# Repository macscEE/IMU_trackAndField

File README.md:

TODO List:
PCB:
- [ ] Cambiare footprint switch da SMD a THT
- [ ] Controllare cosa ho a casa e cosa devo comprare

Programmazione:
- [ ] Capire come far vedere meglio i dati (velocità massima, altezza massima, altro?) -> Sito web al volo?

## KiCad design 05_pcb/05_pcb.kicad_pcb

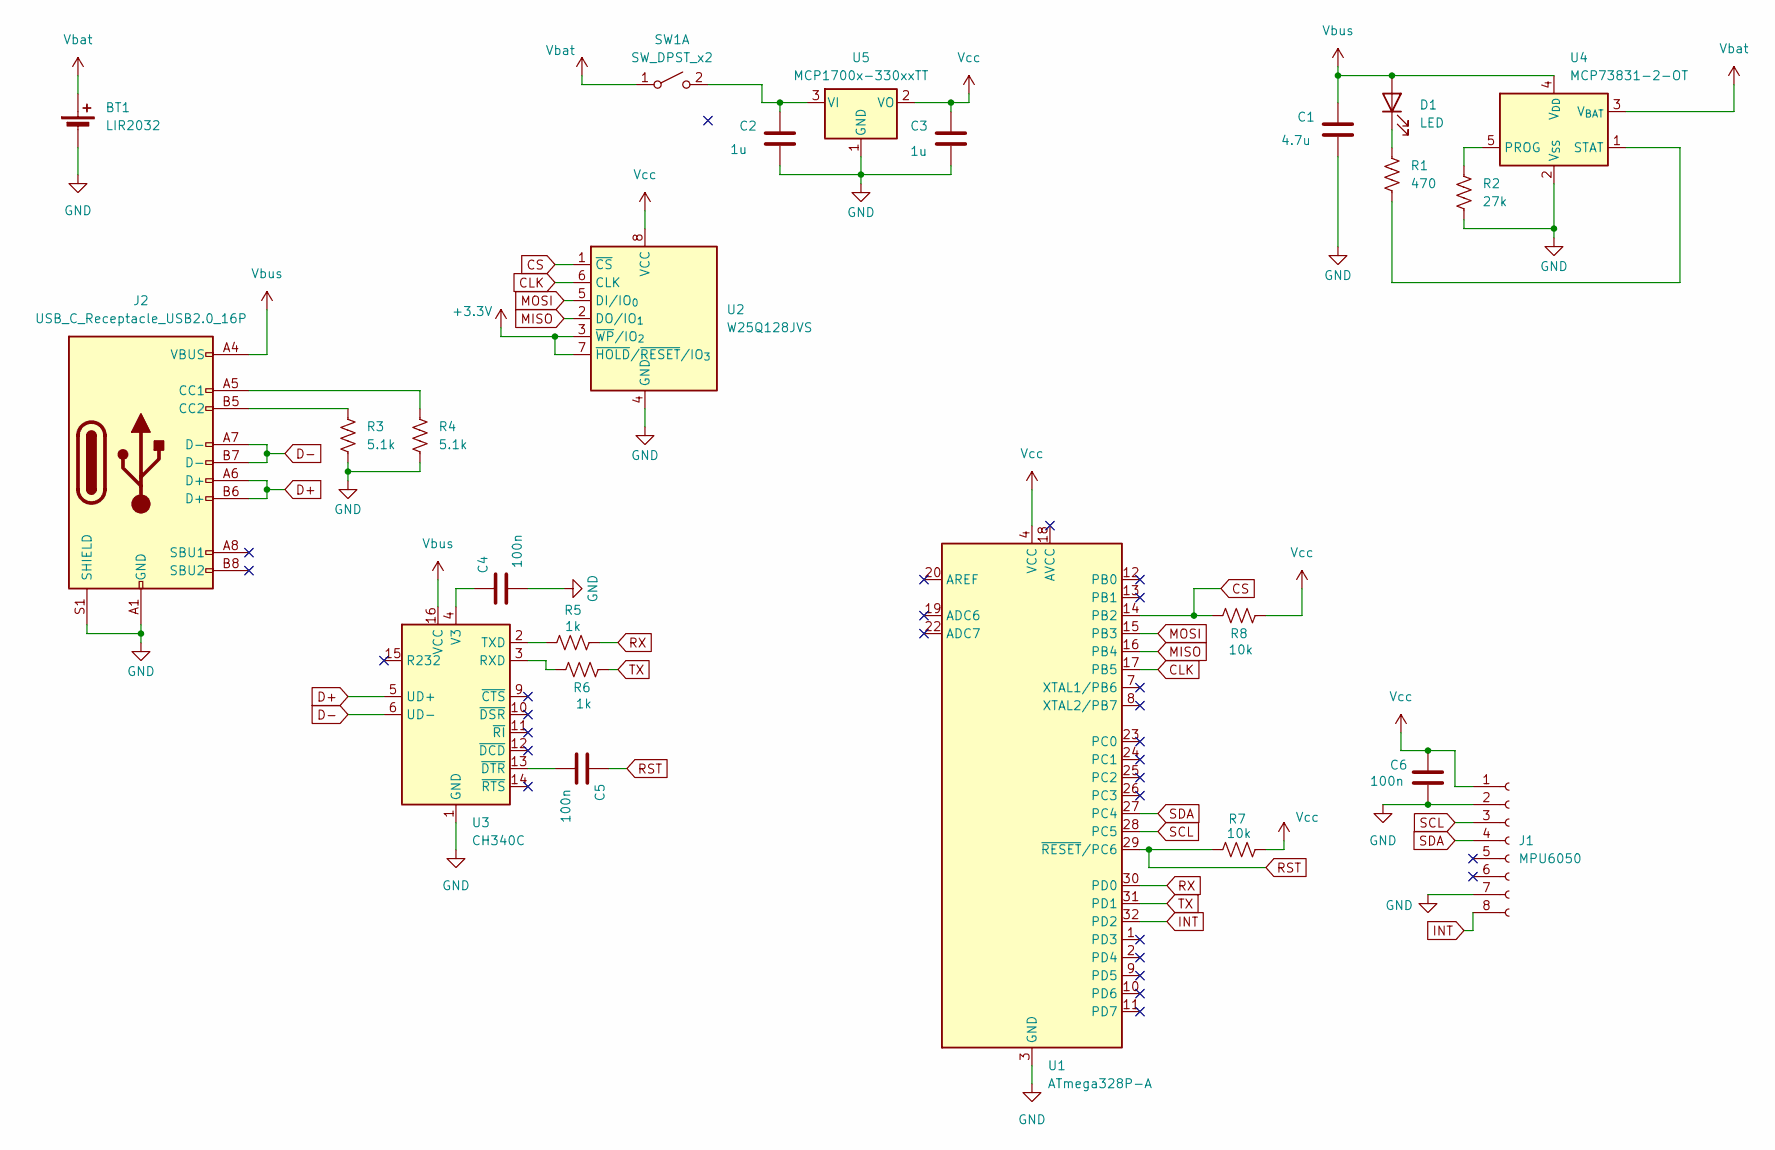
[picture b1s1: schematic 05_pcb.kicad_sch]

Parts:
BT1: LIR2032; BatteryHolder_MYOUNG_BS-07-A1BJ001_CR2032
C1: 4.7u; C_0805_2012Metric
C2, C3: 1u; C_0805_2012Metric
C4, C5, C6: 100n; C_0805_2012Metric
D1: LED; LED_0805_2012Metric
J1: MPU6050; PinSocket_1x08_P2.54mm_Vertical
J2: USB_C_Receptacle_USB2.0_16P; USB_C_Receptacle_HCTL_HC-TYPE-C-16P-01A
R1: 470; R_0805_2012Metric
R2: 27k; R_0805_2012Metric
R3, R4: 5.1k; R_0805_2012Metric
R5, R6: 1k; R_0805_2012Metric
R7, R8: 10k; R_0805_2012Metric
SW1: SW_DPST_x2; SW_DIP_SPSTx01_Slide_6.7x4.1mm_W7.62mm_P2.54mm_LowProfile
U1: ATmega328P-A; TQFP-32_7x7mm_P0.8mm
U2: W25Q128JVS; WSON-8-1EP_8x6mm_P1.27mm_EP3.4x4.3mm
U3: CH340C; SOIC-16_3.9x9.9mm_P1.27mm
U4: MCP73831-2-OT; SOT-23-5
U5: MCP1700x-330xxTT; SOT-23

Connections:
+3.3V: U2.3 (~WP/IO_{2}), U2.7 (~HOLD/~RESET/IO_{3})
CLK: U1.17 (PB5), U2.6 (CLK)
CS: R8.1, U1.14 (PB2), U2.1 (~CS)
D+: J2.A6 (D+), J2.B6 (D+), U3.5 (UD+)
D-: J2.A7 (D-), J2.B7 (D-), U3.6 (UD-)
GND: BT1.2 (-), C1.2, C2.2, C3.2, C4.2, C6.1, J1.2, J1.7, J2.A1 (GND), J2.A12 (GND), J2.B1 (GND), J2.B12 (GND), J2.S1 (SHIELD), R2.2, R3.2, R4.2, U1.3 (GND), U1.5 (GND), U1.21 (GND), U2.4 (GND), U3.1 (GND), U4.2 (V_{SS}), U5.1 (GND)
INT: J1.8, U1.32 (PD2)
MISO: U1.16 (PB4), U2.2 (DO/IO_{1})
MOSI: U1.15 (PB3), U2.5 (DI/IO_{0})
unnamed: D1.1 (K), R1.1
unnamed: J2.A5 (CC1), R4.1
unnamed: J2.B5 (CC2), R3.1
unnamed: C2.1, SW1.2 (B), U5.3 (VI)
unnamed: R6.1, U3.3 (RXD)
unnamed: R5.1, U3.2 (TXD)
unnamed: C4.1, U3.4 (V3)
unnamed: C5.2, U3.13 (~DTR)
unnamed: R2.1, U4.5 (PROG)
unnamed: R1.2, U4.1 (STAT)
RST: C5.1, R7.2, U1.29 (~RESET/PC6)
RX: R5.2, U1.30 (PD0)
SCL: J1.3, U1.28 (PC5)
SDA: J1.4, U1.27 (PC4)
TX: R6.2, U1.31 (PD1)
Vbat: BT1.1 (+), SW1.1 (A), U4.3 (V_{BAT})
Vbus: C1.1, D1.2 (A), J2.A4 (VBUS), J2.A9 (VBUS), J2.B4 (VBUS), J2.B9 (VBUS), U3.16 (VCC), U4.4 (V_{DD})
Vcc: C3.1, C6.2, J1.1, R7.1, R8.2, U1.4 (VCC), U1.6 (VCC), U2.8 (VCC), U5.2 (VO)

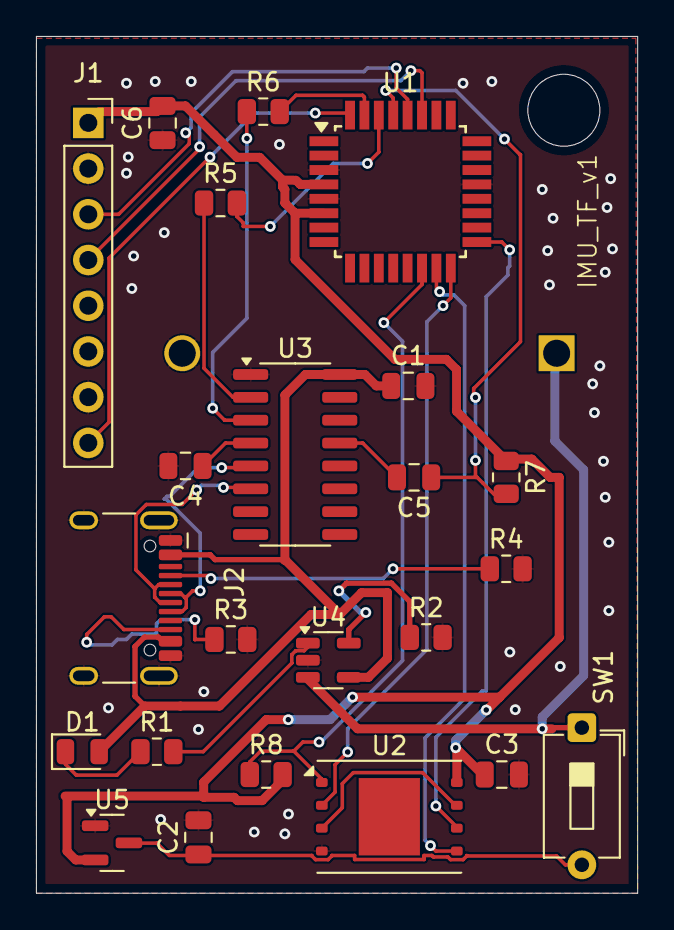
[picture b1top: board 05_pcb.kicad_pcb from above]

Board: 2 copper layers, 33.4 x 47.6 mm, 24 parts (1 on the bottom side), 27 nets.

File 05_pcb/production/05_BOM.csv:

"Id";"Designator";"Footprint";"Quantity";"Designation";"Supplier and ref";
1;"J2";"USB_C_Receptacle_HCTL_HC-TYPE-C-16P-01A";1;"USB_C_Receptacle_USB2.0_16P";;;
2;"SW1";"SW_DIP_SPSTx01_Slide_6.7x4.1mm_W7.62mm_P2.54mm_LowProfile";1;"SW_DPST_x2";;;
3;"U2";"WSON-8-1EP_8x6mm_P1.27mm_EP3.4x4.3mm";1;"W25Q128JVS";;;
4;"C6,C4,C5";"C_0805_2012Metric";3;"100n";;;
5;"R8,R7";"R_0805_2012Metric";2;"10k";;;
6;"J1";"PinSocket_1x08_P2.54mm_Vertical";1;"MPU6050";;;
7;"R2";"R_0805_2012Metric";1;"27k";;;
8;"C2,C3";"C_0805_2012Metric";2;"1u";;;
9;"C1";"C_0805_2012Metric";1;"4.7u";;;
10;"U1";"TQFP-32_7x7mm_P0.8mm";1;"ATmega328P-A";;;
11;"R3,R4";"R_0805_2012Metric";2;"5.1k";;;
12;"U3";"SOIC-16_3.9x9.9mm_P1.27mm";1;"CH340C";;;
13;"R1";"R_0805_2012Metric";1;"470";;;
14;"R6,R5";"R_0805_2012Metric";2;"1k";;;
15;"U4";"SOT-23-5";1;"MCP73831-2-OT";;;
16;"U5";"SOT-23";1;"MCP1700x-330xxTT";;;
17;"D1";"LED_0805_2012Metric";1;"LED";;;
18;"BT1";"BatteryHolder_MYOUNG_BS-07-A1BJ001_CR2032";1;"LIR2032";;;

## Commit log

2026-02-04 IMU setup and initialize of analisys code
2026-02-04 Folder setup adjust
2026-02-04 folder adjust
2026-02-05 Absolute acceleration implementation (still to be tested)
2026-02-06 Plot data and start PCB
2026-02-27 Schematic and PCB update
    Development of the pcb
2026-03-12 Remove project title from README
2026-03-17 Adding envirorment feature
2026-03-17 adding .gitignore
2026-03-17 add git ignore
2026-04-05 PCB complete
2026-04-05 Max speed highlight and update readme file
2026-04-17 New switch footprint and USBC connector
